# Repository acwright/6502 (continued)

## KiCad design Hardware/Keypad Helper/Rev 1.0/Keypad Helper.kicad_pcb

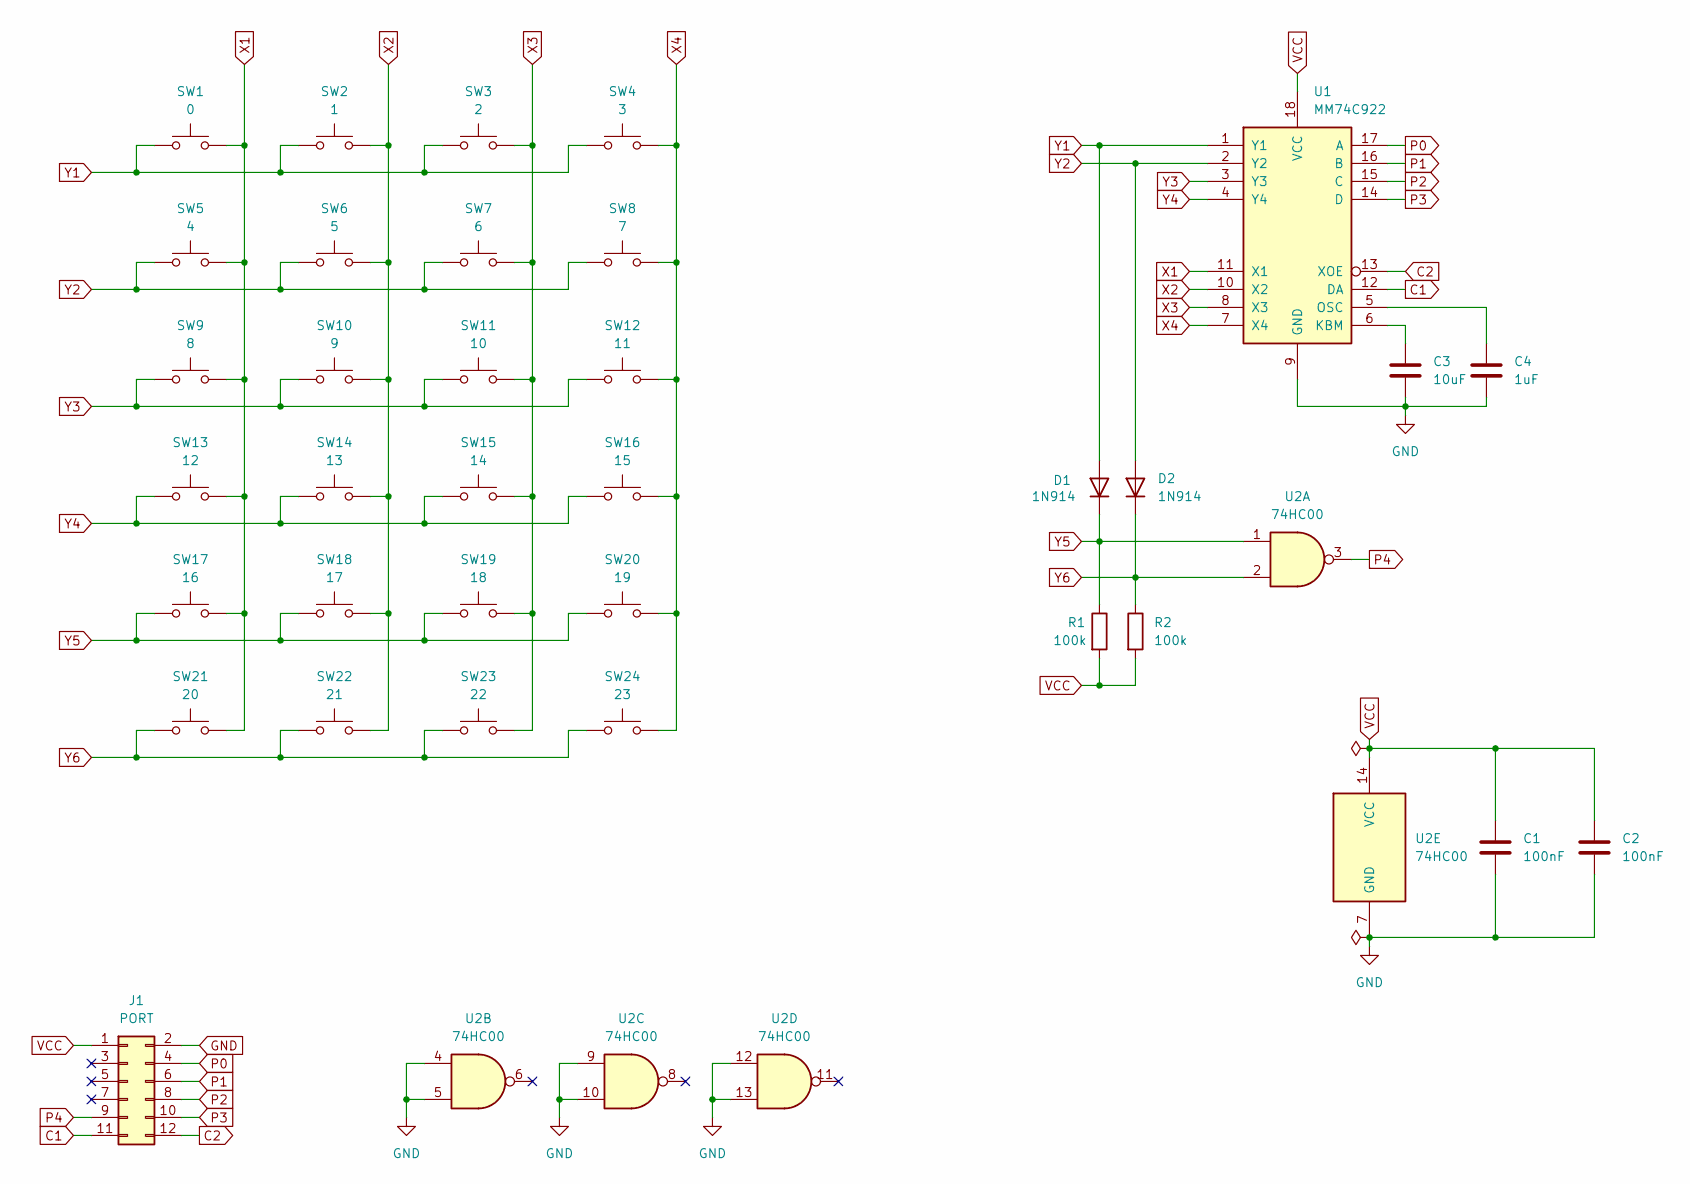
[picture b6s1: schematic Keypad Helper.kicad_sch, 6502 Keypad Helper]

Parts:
C1, C2: 100nF; C_Disc_D5.0mm_W2.5mm_P5.00mm
C3: 10uF; C_Disc_D5.0mm_W2.5mm_P5.00mm
C4: 1uF; C_Disc_D5.0mm_W2.5mm_P5.00mm
D1, D2: 1N914; D_DO-35_SOD27_P7.62mm_Horizontal
J1: PORT; 6502 GPIO Connector
R1, R2: 100k; R_Axial_DIN0204_L3.6mm_D1.6mm_P5.08mm_Horizontal
SW1: 0; SW_Cherry_MX_1.00u_PCB
SW2: 1; SW_Cherry_MX_1.00u_PCB
SW3: 2; SW_Cherry_MX_1.00u_PCB
SW4: 3; SW_Cherry_MX_1.00u_PCB
SW5: 4; SW_Cherry_MX_1.00u_PCB
SW6: 5; SW_Cherry_MX_1.00u_PCB
SW7: 6; SW_Cherry_MX_1.00u_PCB
SW8: 7; SW_Cherry_MX_1.00u_PCB
SW9: 8; SW_Cherry_MX_1.00u_PCB
SW10: 9; SW_Cherry_MX_1.00u_PCB
SW11: 10; SW_Cherry_MX_1.00u_PCB
SW12: 11; SW_Cherry_MX_1.00u_PCB
SW13: 12; SW_Cherry_MX_1.00u_PCB
SW14: 13; SW_Cherry_MX_1.00u_PCB
SW15: 14; SW_Cherry_MX_1.00u_PCB
SW16: 15; SW_Cherry_MX_1.00u_PCB
SW17: 16; SW_Cherry_MX_1.00u_PCB
SW18: 17; SW_Cherry_MX_1.00u_PCB
SW19: 18; SW_Cherry_MX_1.00u_PCB
SW20: 19; SW_Cherry_MX_1.00u_PCB
SW21: 20; SW_Cherry_MX_1.00u_PCB
SW22: 21; SW_Cherry_MX_1.00u_PCB
SW23: 22; SW_Cherry_MX_1.00u_PCB
SW24: 23; SW_Cherry_MX_1.00u_PCB
U1: MM74C922; DIP-18_W7.62mm_Socket_LongPads
U2: 74HC00; DIP-14_W7.62mm_Socket_LongPads

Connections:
C1: J1.11, U1.12 (DA)
C2: J1.12, U1.13 (XOE)
GND: C1.2, C2.2, C3.2, C4.2, J1.2, U1.9 (GND), U2.4, U2.5, U2.7 (GND), U2.9, U2.10, U2.12, U2.13
unnamed: C3.1, U1.6 (KBM)
unnamed: C4.1, U1.5 (OSC)
P0: J1.4, U1.17 (A)
P1: J1.6, U1.16 (B)
P2: J1.8, U1.15 (C)
P3: J1.10, U1.14 (D)
P4: J1.9, U2.3
VCC: C1.1, C2.1, J1.1, R1.2, R2.2, U1.18 (VCC), U2.14 (VCC)
X1: SW1.2, SW5.2, SW9.2, SW13.2, SW17.2, SW21.2, U1.11 (X1)
X2: SW2.2, SW6.2, SW10.2, SW14.2, SW18.2, SW22.2, U1.10 (X2)
X3: SW3.2, SW7.2, SW11.2, SW15.2, SW19.2, SW23.2, U1.8 (X3)
X4: SW4.2, SW8.2, SW12.2, SW16.2, SW20.2, SW24.2, U1.7 (X4)
Y1: D1.2 (A), SW1.1, SW2.1, SW3.1, SW4.1, U1.1 (Y1)
Y2: D2.2 (A), SW5.1, SW6.1, SW7.1, SW8.1, U1.2 (Y2)
Y3: SW9.1, SW10.1, SW11.1, SW12.1, U1.3 (Y3)
Y4: SW13.1, SW14.1, SW15.1, SW16.1, U1.4 (Y4)
Y5: D1.1 (K), R1.1, SW17.1, SW18.1, SW19.1, SW20.1, U2.1
Y6: D2.1 (K), R2.1, SW21.1, SW22.1, SW23.1, SW24.1, U2.2

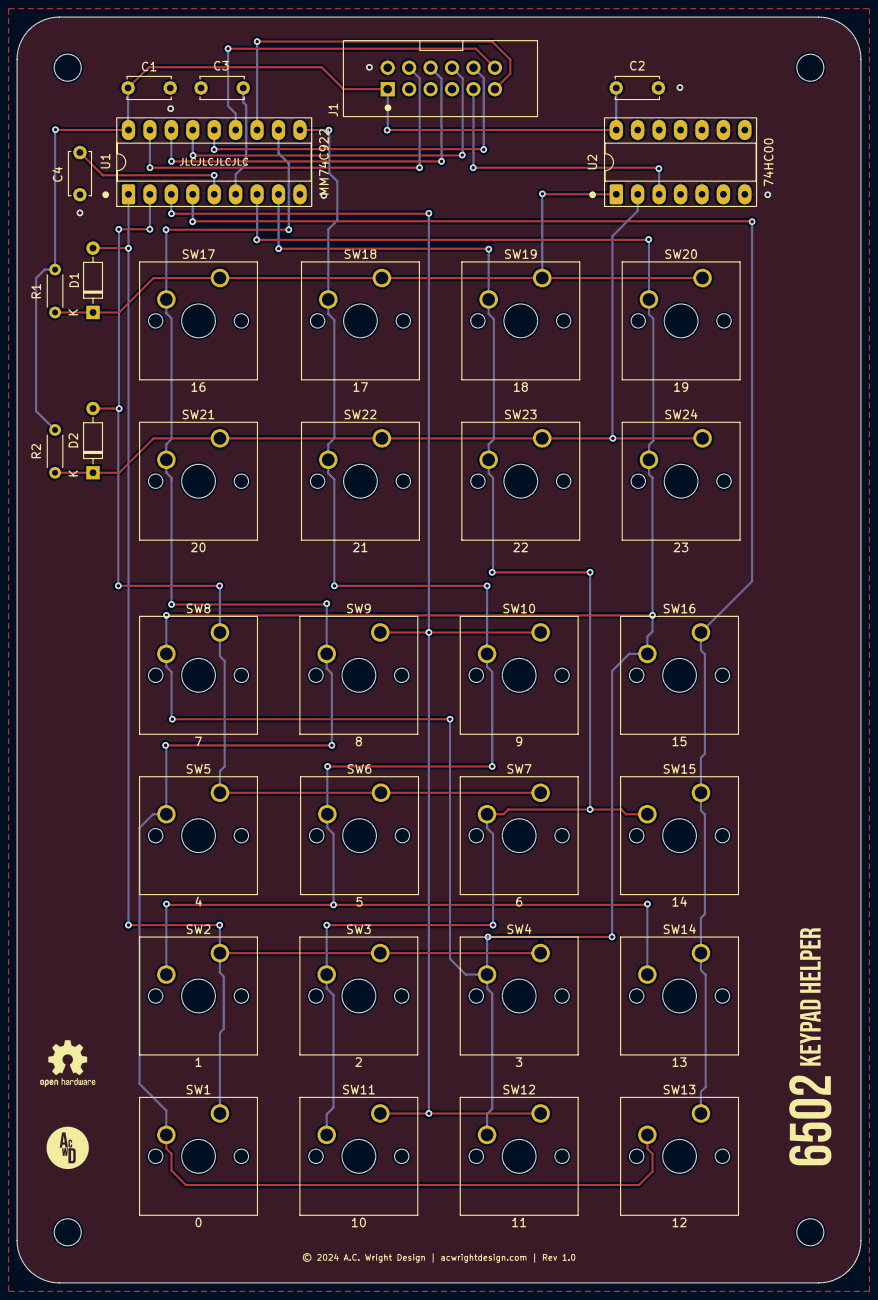
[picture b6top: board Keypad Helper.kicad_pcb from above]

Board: 2 copper layers, 100.0 x 150.0 mm, 39 parts (0 on the bottom side), 21 nets.

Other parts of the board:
H1, H2, H3, H4: MountingHole; MountingHole_3.2mm_M3

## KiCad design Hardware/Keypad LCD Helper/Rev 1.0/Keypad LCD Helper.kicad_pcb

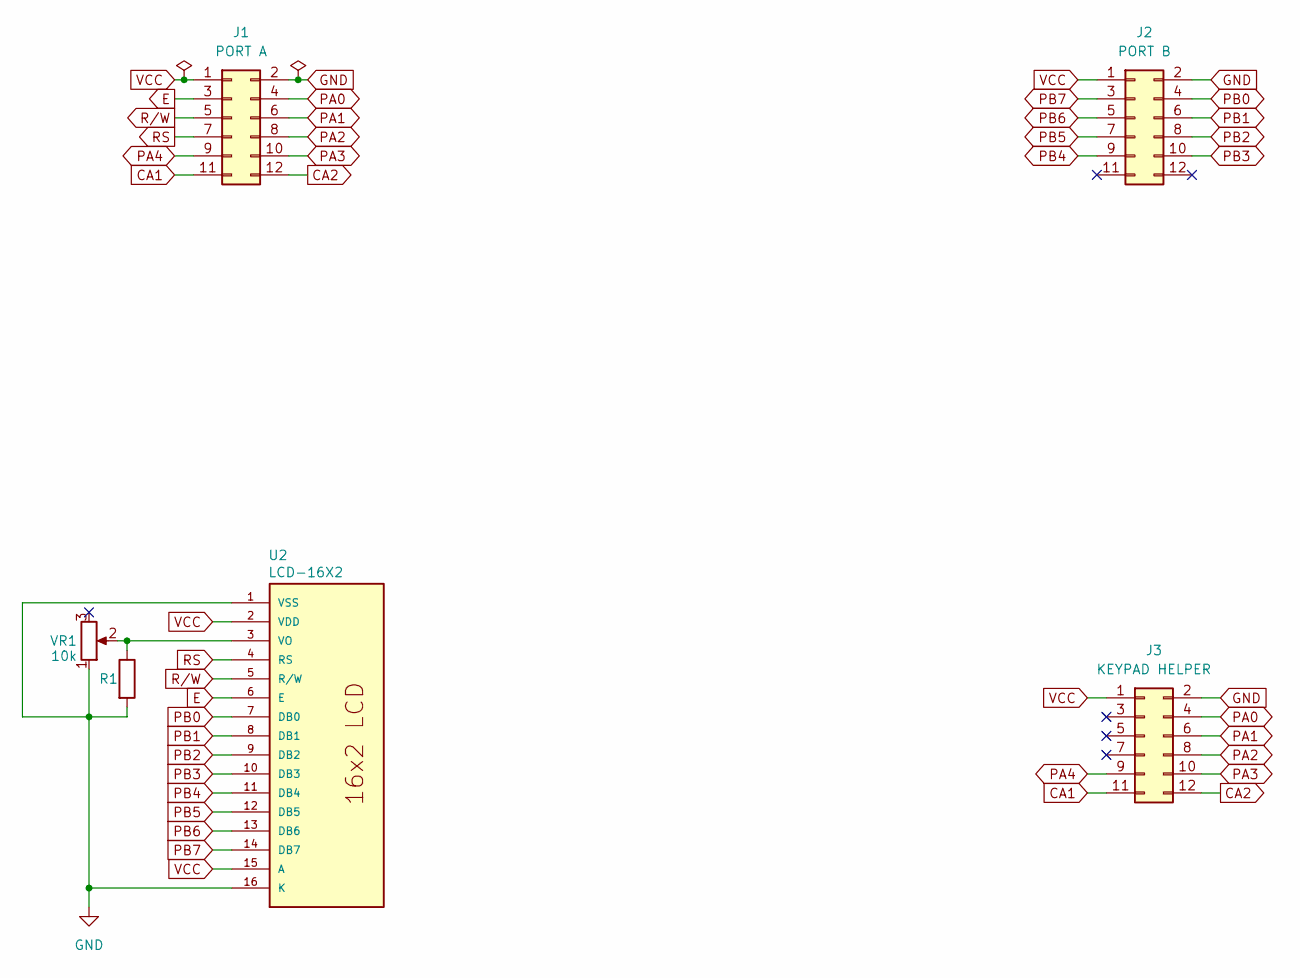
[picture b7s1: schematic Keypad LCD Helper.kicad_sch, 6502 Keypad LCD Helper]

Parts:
J1: PORT A; 6502 GPIO Connector
J2: PORT B; 6502 GPIO Connector
J3: KEYPAD HELPER; 6502 GPIO Connector
R1: R; R_Axial_DIN0204_L3.6mm_D1.6mm_P5.08mm_Horizontal
U2: LCD-16X2; PARTREV N/A
VR1: 10k; 3386F-1-103LF

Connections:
CA1: J1.11, J3.11
CA2: J1.12, J3.12
E: J1.3, U2.6 (E)
GND: J1.2, J2.2, J3.2, R1.2, U2.1 (VSS), U2.16 (K), VR1.1
unnamed: R1.1, U2.3 (VO), VR1.2
PA0: J1.4, J3.4
PA1: J1.6, J3.6
PA2: J1.8, J3.8
PA3: J1.10, J3.10
PA4: J1.9, J3.9
PB0: J2.4, U2.7 (DB0)
PB1: J2.6, U2.8 (DB1)
PB2: J2.8, U2.9 (DB2)
PB3: J2.10, U2.10 (DB3)
PB4: J2.9, U2.11 (DB4)
PB5: J2.7, U2.12 (DB5)
PB6: J2.5, U2.13 (DB6)
PB7: J2.3, U2.14 (DB7)
RS: J1.7, U2.4 (RS)
R/W: J1.5, U2.5 (R/W)
VCC: J1.1, J2.1, J3.1, U2.2 (VDD), U2.15 (A)

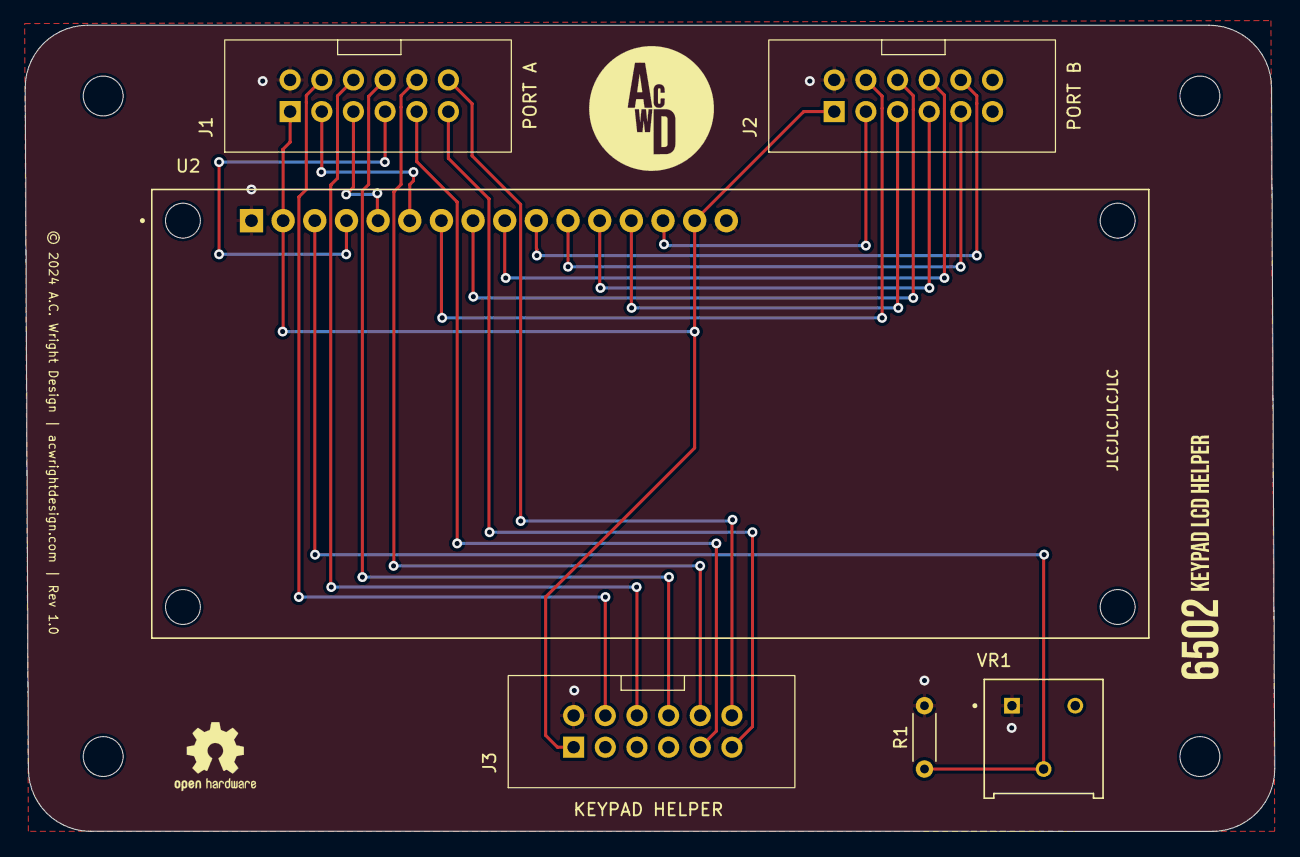
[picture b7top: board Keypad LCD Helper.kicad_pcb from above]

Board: 2 copper layers, 100.3 x 64.7 mm, 10 parts (0 on the bottom side), 21 nets.

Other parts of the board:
H1, H2, H3, H4: MountingHole; MountingHole_3.2mm_M3
